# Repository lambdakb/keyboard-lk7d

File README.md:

# LK7D 7 Keys Macropad

The LambdaKB LK7D is a simple 7 keys hotswap macropad with per-key RGB LEDs and an OLED display. The goal was to create a simple macropad based on the XIAO RP2040 microcontroller that had all the bells and whispers of a modern keyboard.

This was created as an experiment to learn more about designing PCBs and to have a simple and cheap way to test new features (such as integrating OLED displays and RGB LEDs in QMK / Vial).

## Layout

[Keyboard Layout Editor](https://www.keyboard-layout-editor.com/##@_css=.keyborder%5Bstyle*%2F=%22%23ff0000%22%5D%20%7B%0A%20%20%20%20border-radius%2F:%2050%25%20!important%2F%3B%0A%20%20%20%20background-color%2F:%20%23ccc%20!important%2F%3B%0A%7D%0A.keytop%5Bstyle*%2F=%22%23ff4223%22%5D%20%7B%0A%20%20%20%20border-radius%2F:%2050%25%20!important%2F%3B%0A%20%20%20%20background-color%2F:%20%23fff%20!important%2F%3B%0A%7D%3B&@_x:2&c=%23ff0000&p=CHICKLET&a:7%3B&=E%3B&@_y:-0.9&c=%23cccccc&p=FLAT&w:2&h:0.8%3B&=OLED%3B&@_y:-0.10000000000000009&p=R1%3B&=M0&=M1&=M2%3B&@=M3&=M4&=M5)

## PCB

|             Front             |            Back             |
| :---------------------------: | :-------------------------: |
| [![PCB Front]][PCB Front PNG] | [![PCB Back]][PCB Back PNG] |

[PCB Front]: output/pcb/img/lk7d-pcb-top.svg
[PCB Front PNG]: output/pcb/img/lk7d-pcb-top.png
[PCB Back]: output/pcb/img/lk7d-pcb-bottom.svg
[PCB Back PNG]: output/pcb/img/lk7d-pcb-bottom.png

The PCB has been designed in [KiCad EDA 9.0](https://www.kicad.org/) using the [`kicad-lkbd`](https://github.com/lambdakb/kicad-lkbd) libraries.

You can preview the project files using [KiCanvas](https://kicanvas.org/?github=https%3A%2F%2Fgithub.com%2Flambdakb%keyboard-lk7d%2Fblob%2Fmain%2Fpcb%2Flk7d-pcb.kicad_pro) directly in your browser and download the latest fabrication files for JLCPCB from the [latest release](https://github.com/lambdakb/trackball-lk7d/releases/latest/).

The exported schematic is also available under [`output/schematics`](output/schematics/).

### PCB Order

| Parameters                       | Value                  |
| -------------------------------- | ---------------------- |
| Base Material                    | FR4                    |
| Layers                           | 2                      |
| Dimensions                       | 57.15 × 57.15 mm       |
| PCB Thickness                    | 1.6 mm                 |
| PCB Color [^pcb-color]           | Black                  |
| Silkscreen                       | White                  |
| Surface Finish [^surface-finish] | Lead Free HASL or ENIG |
| Copper Weight                    | 1 oz                   |
| Via Covering                     | Tented                 |
| Min Via Hole Size                | 0.3 mm                 |
| Board Outline Tolerance          | ± 0.2 mm               |

[^pcb-color]: You can select any PCB color you want but some manufacturers such as JLCPCB may charge you more for uncommon combos (such as Blue PCB + ENIG Surface Finish).
[^surface-finish]: The "HASL (with lead)" option is extremely discouraged due to the risk of lead poisoning. We strongly recommend paying the premium for the "Lead Free HASL" option.

### BOM

| Part                     | Ref.                                                | Quantity | Optional | Remarks                                                                                                                                                   |
| ------------------------ | --------------------------------------------------- | :------: | :------: | --------------------------------------------------------------------------------------------------------------------------------------------------------- |
| PCB                      | [LK7D PCB](./pcb/)                                  |    1     |    ❌    | The PCB itself.                                                                                                                                           |
| XIAO RP2040 Controller   | [SeeedStudio XIAO RP2040]                           |    1     |    ❌    | Main controller for QMK/Vial.                                                                                                                             |
| 1N418 Diodes             | [1N4148W T4 SOD-323]                                |    7     |    ❌    | Switch matrix diodes. One MUST be installed under the encoder.                                                                                            |
| Kailh Hot-Swap Sockets   | [CPG151101S11-16]                                   |    6     |    ❌    | MX style hot-swap sockets.                                                                                                                                |
| Key Switches             | Any [Cherry MX] Compatible Switch                   |    6     |    ❌    | MX style switches.                                                                                                                                        |
| Rotary Encoder           | Any [EC11] / [EC12] style 5-pin Encoder             |    1     |    ❌    | Can be installed either in top left or top right of the PCB. Only one per PCB is supported.                                                               |
| 100nF Capacitor          | [1206 SMD Ceramic Capacitor]                        |   2-3    |    ✅    | Both C1 and C2 should be installed if populated, used for noise filtering of encoder readings. C3 is only required if a Logic Level Shifter is installed. |
| 0.91" OLED Display       | [SSD1306 0.91" 128X32 OLED I²C Display Module]      |    1     |    ✅    | Optional, occupies the place of the non-populated encoder and sits on top of the XIAO MCU.                                                                |
| RGB LEDs                 | [SK6812MINI-E]                                      |    6     |    ✅    | Optional, RGB LEDs can be installed under each key switch.                                                                                                |
| 5V Logic Level Converter | [SN74AHCT1G125DBVR] or [SN74LV1T125DBVR] (SOT-23-5) |    1     |    ✅    | Optional, required if your RGB LEDs are not 3.3V logic tolerant. You MUST cut the JP1 jumper if populated.                                                |

[SeeedStudio XIAO RP2040]: https://www.seeedstudio.com/XIAO-RP2040-v1-0-p-5026.html
[1N4148W T4 SOD-323]: https://www.aliexpress.com/item/1005006127619725.html
[CPG151101S11-16]: https://www.aliexpress.com/item/1005007052649640.html
[Cherry MX]: https://www.aliexpress.com/item/1005006255961111.html
[EC11]: https://www.aliexpress.com/item/32382989585.html
[EC12]: https://www.aliexpress.com/item/1005005196870256.html
[1206 SMD ceramic capacitor]: https://www.aliexpress.com/item/32966490820.html
[SSD1306 0.91" 128X32 OLED I²C Display Module]: https://www.aliexpress.com/item/32777216785.html
[SK6812MINI-E]: https://www.aliexpress.com/item/1005006473087141.html
[SN74AHCT1G125DBVR]: https://www.aliexpress.com/item/1005005379322968.html
[SN74LV1T125DBVR]: https://www.digikey.com/en/products/detail/texas-instruments/SN74LV1T125DBVR/4555571

## Case

Coming soon.

## Firmware

The pre-build firmware available in this repository are compiled using [Vial](https://get.vial.today/) (a fork of [QMK](https://qmk.fm) allowing customization via a GUI).

As per the original license of both Vial and QMK, the firmware itself is licensed under the GPLv3 license and its source code is available at [`vial-qmk/keyboards/lambdakb/lk7d`](https://github.com/lambdakb/vial-qmk/tree/lambdakb/keyboards/lambdakb/lk7d).

### Default Vial Keymap

| Layer 0           | Layer 1           | Layer 2           | Layer 3           |
| ----------------- | ----------------- | ----------------- | ----------------- |
| ![Keymap Layer 0] | ![Keymap Layer 1] | ![Keymap Layer 2] | ![Keymap Layer 3] |

[Keymap Layer 0]: assets/vial-default-layer0.png
[Keymap Layer 1]: assets/vial-default-layer1.png
[Keymap Layer 2]: assets/vial-default-layer2.png
[Keymap Layer 3]: assets/vial-default-layer3.png

Layer 4, 5 and 6 contains similar layouts with macro keys going from M15 to M29.

### Vial Layout Options

| Encoder Position: Left | Encoder Position: Right |
| ---------------------- | ----------------------- |
| ![Layout Encoder Left] | ![Layout Right Encoder] |

[Layout Encoder Left]: assets/vial-layout-enc-left.png
[Layout Right Encoder]: assets/vial-layout-enc-right.png

## License

This design is licensed under the [CERN Open Hardware Licence Version 2 – Strongly Reciprocal (CERN-OHL-S-2.0)](https://opensource.org/license/cern-ohl-s).

You are free to use, modify, and distribute this design for any purpose, provided that:

- **Attribution**: Appropriate credit is given, a link to the license is provided, and any modifications are clearly indicated.
- **Reciprocity**: Any derivative works must be released under the same license.

If you are a retailer or business interested in producing or selling this design or related products, I’d love to discuss it! Please feel free to reach out so we can explore potential arrangements.

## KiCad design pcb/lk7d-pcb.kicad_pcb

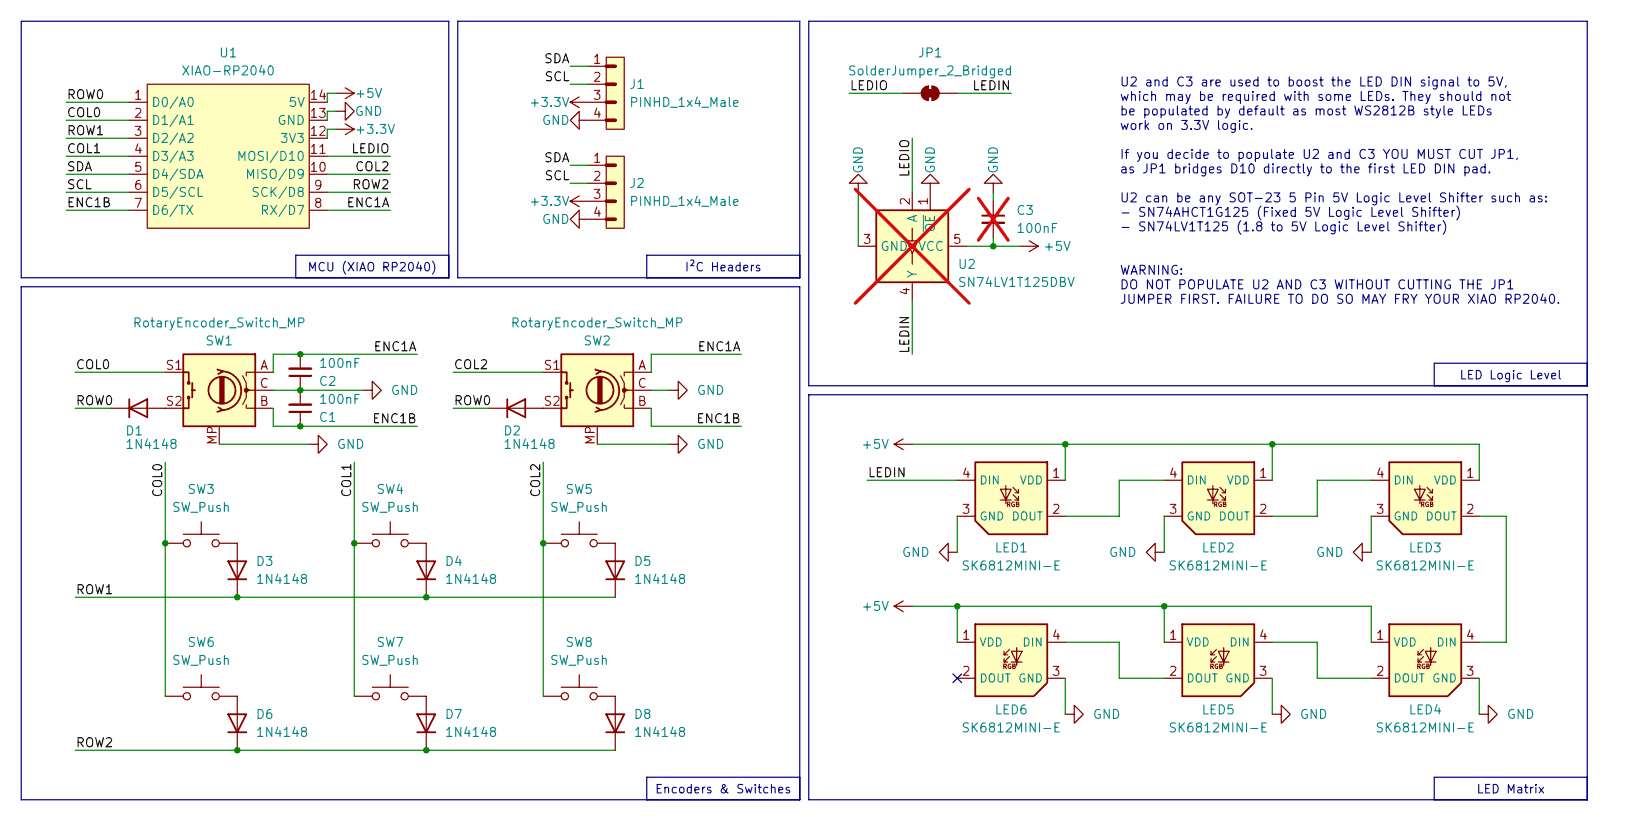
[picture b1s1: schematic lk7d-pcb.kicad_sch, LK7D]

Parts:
C1, C2: 100nF; Capacitor_SMD_1206_inSilk; LCSC C24497
C3: 100nF; Capacitor_SMD_1206_inSilk; JLC 1206; not fitted
D1, D2, D3, D4, D5, D6, D7, D8: 1N4148; Diode_SMD_SOD-123_inSilk; LCSC C81598
J1, J2: PINHD_1x4_Male; PinHeader_1x04_P2.54mm_Vertical
JP1: SolderJumper_2_Bridged; SolderJumper-2_P1.3mm_Bridged_RoundedPad1.0x1.5mm
LED1, LED2, LED3, LED4, LED5, LED6: SK6812MINI-E; LED_SK6812MINI-E; JLC SMD
SW1, SW2: RotaryEncoder_Switch_MP; EC11_THT_sqSilk
SW3, SW4, SW5, SW6, SW7, SW8: SW_Push; SW_MX_HotSwap_sqSilk; JLC SMD
U1: XIAO-RP2040; MCU_XIAO-RP2040; JLC SMD-14P
U2: SN74LV1T125DBV; SOT-23-5; JLC SOT-23-5; not fitted

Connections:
+3.3V: J1.3, J2.3, U1.12 (3V3)
+5V: C3.2, LED1.1 (VDD), LED2.1 (VDD), LED3.1 (VDD), LED4.1 (VDD), LED5.1 (VDD), LED6.1 (VDD), U1.14 (5V), U2.5 (VCC)
/COL0: SW1.S1, SW3.1, SW6.1, U1.2 (D1/A1)
/COL1: SW4.1, SW7.1, U1.4 (D3/A3)
/COL2: SW2.S1, SW5.1, SW8.1, U1.10 (MISO/D9)
/ENC1A: C2.2, SW1.A, SW2.A, U1.8 (RX/D7)
/ENC1B: C1.1, SW1.B, SW2.B, U1.7 (D6/TX)
/LEDIN: JP1.2 (B), LED1.4 (DIN), U2.4 (Y)
/LEDIO: JP1.1 (A), U1.11 (MOSI/D10), U2.2 (A)
/ROW0: D1.1 (K), D2.1 (K), U1.1 (D0/A0)
/ROW1: D3.1 (K), D4.1 (K), D5.1 (K), U1.3 (D2/A2)
/ROW2: D6.1 (K), D7.1 (K), D8.1 (K), U1.9 (SCK/D8)
/SCL: J1.2, J2.2, U1.6 (D5/SCL)
/SDA: J1.1, J2.1, U1.5 (D4/SDA)
GND: C1.2, C2.1, C3.1, J1.4, J2.4, LED1.3 (GND), LED2.3 (GND), LED3.3 (GND), LED4.3 (GND), LED5.3 (GND), LED6.3 (GND), SW1.C, SW1.MP, SW2.C, SW2.MP, U1.13 (GND), U2.1 (~OE), U2.3 (GND)
unnamed: D1.2 (A), SW1.S2
unnamed: D2.2 (A), SW2.S2
unnamed: D3.2 (A), SW3.2
unnamed: D4.2 (A), SW4.2
unnamed: D5.2 (A), SW5.2
unnamed: D6.2 (A), SW6.2
unnamed: D7.2 (A), SW7.2
unnamed: D8.2 (A), SW8.2
unnamed: LED1.2 (DOUT), LED2.4 (DIN)
unnamed: LED2.2 (DOUT), LED3.4 (DIN)
unnamed: LED3.2 (DOUT), LED4.4 (DIN)
unnamed: LED4.2 (DOUT), LED5.4 (DIN)
unnamed: LED5.2 (DOUT), LED6.4 (DIN)

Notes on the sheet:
LED Matrix
U2 and C3 are used to boost the LED DIN signal to 5V, which may be required with some LEDs. They should not be populated by default as most WS2812B style LEDs work on 3.3V logic. If you decide to populate U2 and C3 YOU MUST CUT JP1, as JP1 bridges D10 directly to the first LED DIN pad. U2 can be an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
MCU (XIAO RP2040)
I²C Headers
LED Logic Level
Encoders & Switches

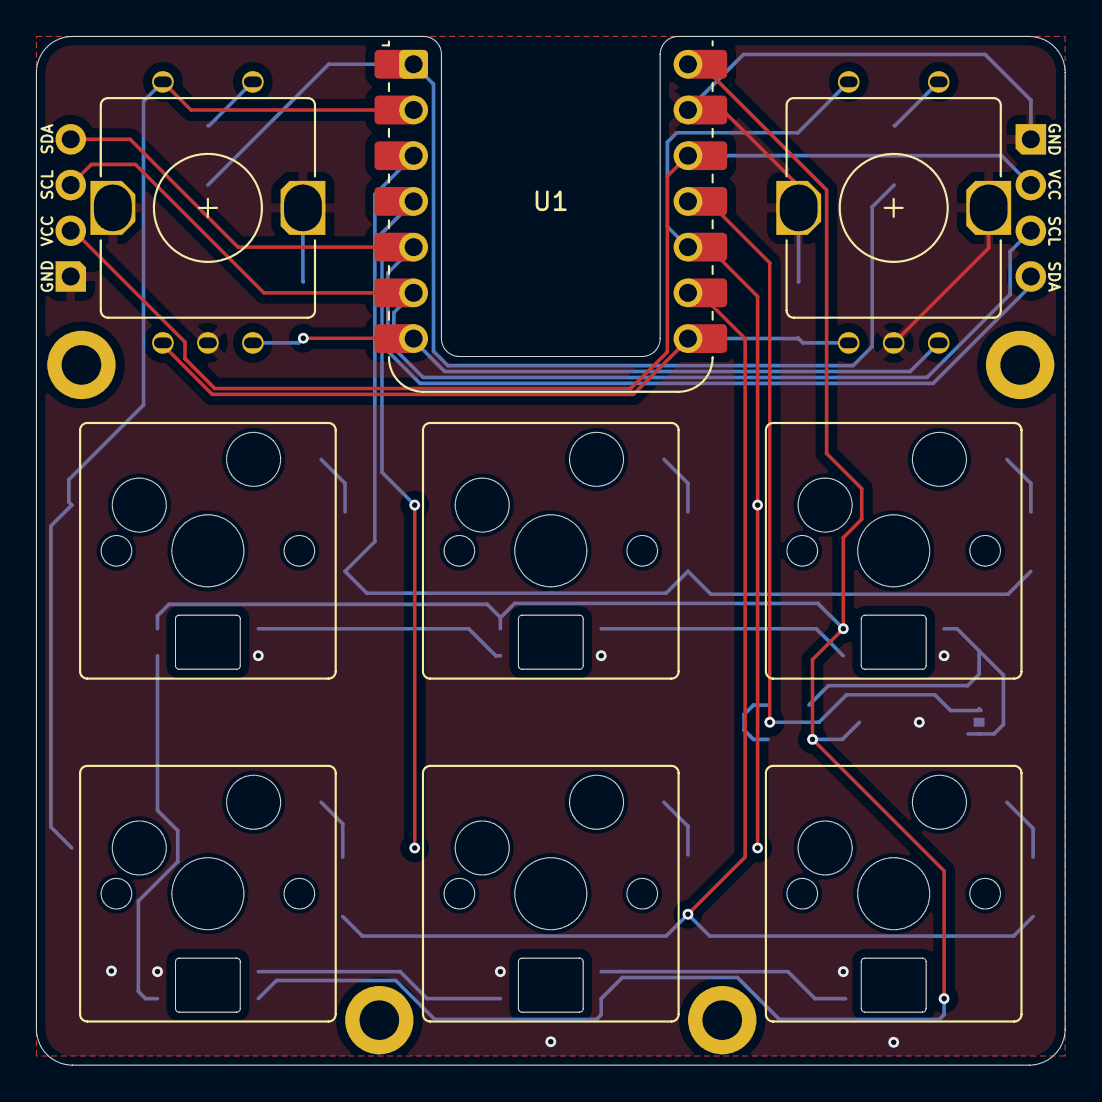
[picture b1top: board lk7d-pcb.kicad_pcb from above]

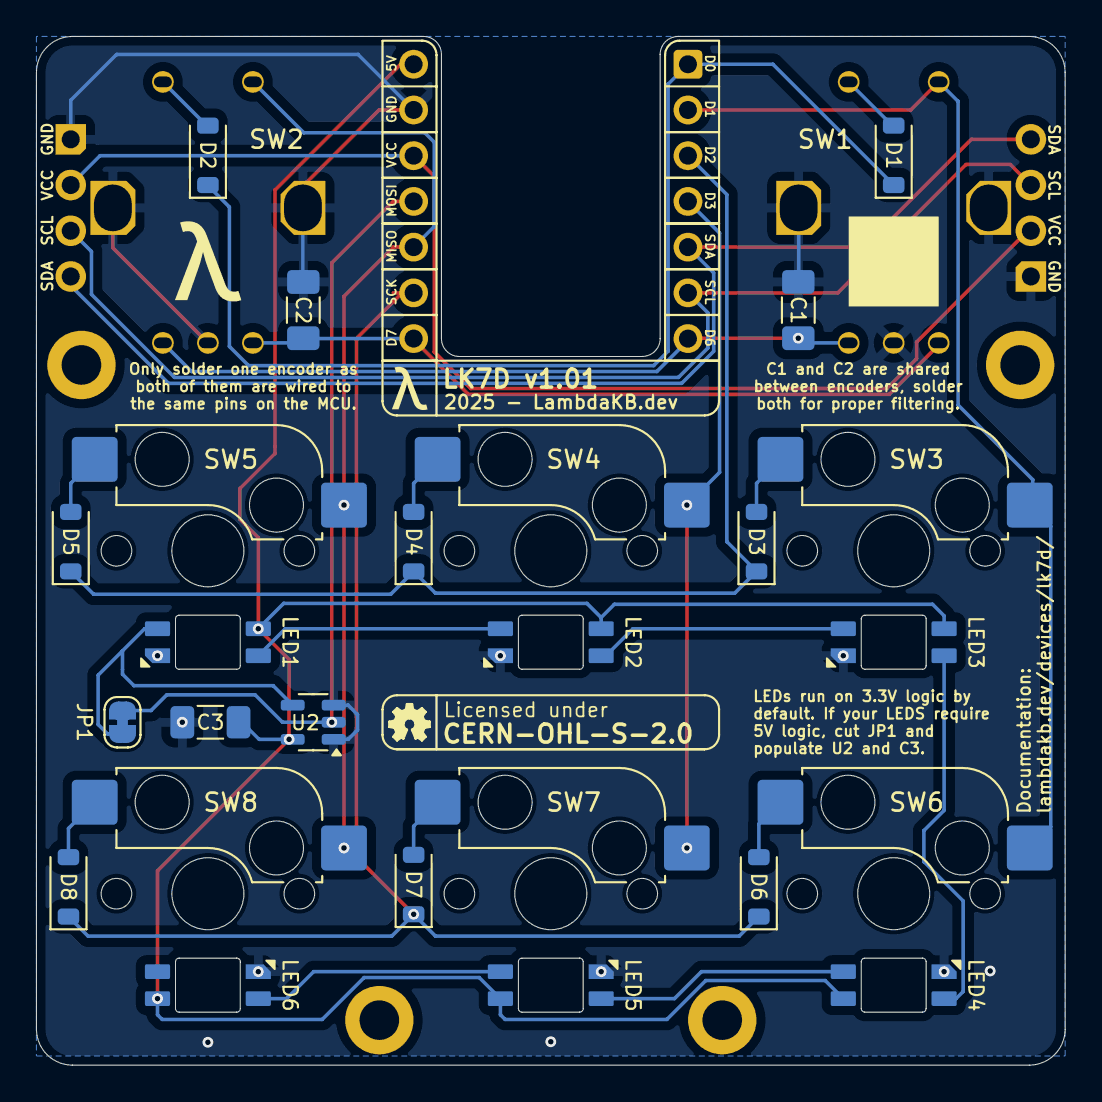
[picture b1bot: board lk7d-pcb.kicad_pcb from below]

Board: 2 copper layers, 57.2 x 57.2 mm, 35 parts (26 on the bottom side), 28 nets.

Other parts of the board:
H1, H2, H3, H4: MountingHole_2.2mm_M2_ISO14580_Pad
M1: JLCPCB_2DBarcode_5x5mm

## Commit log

2025-03-24 Initial LK7D prototype
2025-03-24 Update silkscreen
2025-03-25 Export
2025-03-28 Fix Data Matrix Code positioning following JLCPCB feedbacks
2025-03-28 Fix Data Matrix Code positioning (#1)
    Fix Data Matrix Code positioning following JLCPCB feedbacks
2025-03-28 Add BOM to README.md
2025-03-28 Add BOM to README.md (#2)
2025-04-08 Add Logic Level Converter for per keys LEDs
2025-04-10 Fix SK6812MINI-E pin mapping
2025-04-10 Add Logic Level Converter for per key LEDs (#3)
2025-04-12 Add plate and cleanup PCB
2025-04-12 Add plate and cleanup PCB (#4)
2025-04-12 Add missing components to BOM
2025-04-12 Add missing components to BOM (#5)
2025-04-12 Make the plate a separate PCB
2025-04-12 Format README.md
2025-04-12 Make plate a separate PCB (#6)
    * Make the plate a separate PCB
    * Update PCB 3D models and add layout to README.md
    * Format README.md
2025-04-12 Fix plate image export
2025-04-12 Fix plate export (#7)
2025-04-14 Add Vial firmware details
2025-04-14 Add Vial firmware details (#8)
2025-05-13 Update LKBD libraries
2025-05-13 Update LKBD libraries (#9)

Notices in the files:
README.md:
License: CERN-OHL-S-2.0
